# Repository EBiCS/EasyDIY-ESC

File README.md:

# EasyDIY ESC

Note: 'main' branch is under development, there is a change to use KiCad as compared to v0.5.2 (current HEAD of feature/v0_5_2, i.e. git SHA1 - e55e314)

The target for this EV motor controller is to power small EVs like EBikes or EScooters like Xiaomi M365, and offer better customizability and repairability.

## Main objectives:

* **Easy to build and repair DIY**: It uses DC-DC modules, a development board instead of an uC chip, SMD passive components are all 0805 or bigger, and ICs are SOIC8 or SOIC14. No fine pitch components.

* **Popular components:** Uses the popular Bluepill STM32F103 board, meaning it is easy to develop firmware for it. Uses popular components / footprints / pinouts. Meaning you should have no problems with part availability, and if you do, you will be able to change most parts with equivalents depending on availability or prefrence, without need to change the pcb layout.

* **Possible to add custom electronics:** For reusing this motor controller on different devices, you can extend the electrocnis with a custom header on top of the Bluepill. This means you can use all available pins and access and extend with: CAN, UARTs, etc.

* **Possibility to buy the SMD parts pre-soldered:** While we went to great extend do make this board easy to DIY by humans (as opposed to robots in a factory), we acknowledge there are many who lack the skill/time/motivation to solder all SMDs themselves. So all SMDs are on the same side, in large stock at lcsc (at the time of writing), so the board can be ordered with SMDs pre-assembled by JLCPCB for a decent price.

* **Compactness:** Despite using only big DIY friendly parts, we tried to keep the board as small as possible: ~ 73mm x 49mm

* **Good Power/Size ratio:** Our initial estimation (untested) is that the upper limit for phase current should be ~78A. As for max continuous “battery amps”, it heavily depends on the cooling!  

## ES Thread:
https://endless-sphere.com/forums/viewtopic.php?f=30&t=114537

## Building Tips:

### **Bus Bars**
Bus bars are recommended for anything else than very low current. (extra copper wires soldered to the exposed copper strips of the PCB, or at very least a lot of solder on the exposed strips)

### **Bulk electrolytic capacitors (XC.... )**
We went for a total of ~1000uF, which should be enough for most usecases. 
You need more capacitance the more power you plan to use, and the longer (and thinner) your battery wires are. So you can probably also get away with less if you have short thick battery wires.  
Choose voltage rating ~ 1.5x your max battery voltage for a long lifetime. For 48v nominal (54.6V max) battery voltage, 80V or more is recommended. 
The total capacitance of the electrolytic capacitors is more important than the exact combination of values. 1 big + 3 small is almost the same as 3 medium of the same total value. More smaller capacitors have the advantage of lower ESR, lower inductance, and redundancy in case one fails)

### **Bulk ceramic/MLC capacitors:  (XC.... )**
As much as possible. These need to compensate for the high frequency weakness of the electrolytic capacitors. Overrating voltage rating is recommended. (author chose 100V for the “default” for 3.3v, 5v and 12v). Definitely fill all open footprints. 

### **Capacitors - the rest**
Values are consolidated for easy buying. Voltage rating is 25V or higher regardless if they are on the 12v, 5v, or 3v3 rail on the default design, however you can choose a smaller voltage rating for the 5v and 3v3 rails..  
All parts are 0805 mlc (2 electrolytic exceptions, C8 and C10 from the 12v and 5v rails)

### **Snubbers (RSx, CSx)**
These are RC snubbers. **The current values for the R and C are random, they are here only for the footprints. Do not fit them (yet).** The real values (if necessary at all) will be computed after we build the controller and see what ringing we get. Purpose of the snubbers is to dampen that ringing. (if you choose different parts than the one we compute the snubbers for, you might need to compute the snubbers yourself). These components are not present in the pick-and-place or BOM files.

### **Optional Capacitors (OCx)**
All parts marked OCx are optional GS Capacitors for the mosfets. If you insist on using old/bad mosfets with high Crss, you'll need to compensate for that with additional Cgs. That being said, please avoid high Crss mosfets, and you don't need to use the OCx. We expect none of the recommended FETs to need these. These are footprints only to offer flexibility if needed. These components are not present in the pick-and-place or BOM files. 

### **FETs**
The default FETs are available from aliexpress at the time of writing. They are cheap and have good specs. (low Rds on, low Crss, 100v, etc). 
You can solder them “standing” on the the throughhole/module side, or bent flat on the opposite (smd) side. In either case, it is recommended that the thick part of the leads is in contact with (soldered to) the board. The thin part of the leads can carry significantly less current.

You can use a fet of your choosing, but please be aware that old Fets (such as the famous 4110 or 3077) have huge Crss, leading to a tiny Ciss/Crss ratio. This ratio needs to be bigger than roughly your max battery voltage, so you will need to compute and add the optional Cgs capacitors (OCx). Small Ciss/Crss results in ringing / parastic turn on (which leads to failure). 
That being said, it’s best to just use Fets with Ciss/Crss > ~100, nowadays they’re easy to find. See the spreadsheet with alternative parts. 

Attaching the FETs to a heatsink: the FETs need to be electrically isolated from the heatsink, but well connected thermally. The options for this are:
* Mica glass (“traditional option”, cheap, easy to find)
* Ceramics (saw this as a new option, never tried it)
* Polymer pads 
* Kapton Tape 

Unfortunately in focusing on making the board small we crammed the FETs very close together. This means some mica or ceramic pads will not fit - and it’s very hard to cut them afaik. So for this version we’re probably stuck with polymer / kapton. 

### **Testing**

* v0.5 build has been tested by mxlemming with MESC FOC firmware on F401CC black pill board

### **Known issues/limitations:**
* Mosfet temp sensor missing - you can add it to the expansion board. 
* Many connectors are not present (example: CAN)  - you can add them to the expansion board. 

## FAQ

* **What’s with those 2 solder jumpers?**
They are power for your uart-connected board. If it’s a 5v board, solder the 5v solder jumper, if it needs 3.3v solder the 3v3 jumper. Never solder both! 

* **Can you assemble it for me?**
You can get the SMD side pre-assembled at jlcpcb (at the time of design all parts were in stock for jlcpcb SMT service). So you’ll only need to solder the through-hole parts and the modules. Currently there is no plan on selling any assembled PCBs.

* **I want more power!!!**
This might not go well. So good luck, you’ll probably need it. Please don't blame us when it goes up in smoke. But do let us know how it goes. Disclamer aside, here are some basic suggestions:
   * Stack another 1mohm shunt on top of the other. This will double the max current you can read. 
   * Add thick bus bars to the board.
   * Add more/ bigger bulk caps!
   * Use appropriate wires (thick!) 

* **I want more voltage!!!!**
Realistic limit is 15s lipo. For more than that the ESC will need serious redesign.
Some bottlenecks that cross my mind: 
   * default 12v dc module is 72v limited, 
   * some of the recommended mosfets are not capable of more voltage, 
   * voltage sense divider needs adjustment, etc. 
   * PS: I would have loved to make it 20s capable, but did not find any small 100-12v DC-DC module. If you know of one, please let us know in our ES thread, and next version might be 20s / 74v capable. Also, I added 3 through hole pads for easy mounting of any 12V module via wires :)

* **Your part X is bad, I recommend Y!**
We tried to find cheap but decent parts for this controller. Cheap almost always implies a compromise in some other areas, so you might not like our pick :)
It should be fairly easy to switch to other parts on your own: we used mostly standard and popular footprints and packages
If you know better parts or have better solutions, please let us know on our ES thread. We like learning new things. 
....except if you’re going to suggest 3077 or 4110 mosfets. Those things are dinosaurs. They were the biggest baddest thing around during their time, but nowadays belong to a museum. Or a kid’s t-shirt. Please stop recommending them. See our thread for details.

* **Where can I buy parts?**
Lcsc.com, mouser.com. Aliexpress if needed. 
I designed this with jlcpcb smt assembly in mind, so all SMDs were in stock at lcsc when I designed the PCB. Also most of the Through-hole parts. 
Some exceptions, and where to buy them:
   * Default mosfets - aliexpress. 
   * 12v module - mouser
   * 5v module - aliexpress. There is a fixed voltage one, we recommend that one! 
   * Bluepill - aliexpress. Don’t know a better source these days. 
   * Jst headers - aliexpress
   * Bluepill headers - aliexpress

* **Why do the battery wires go in seemingly random places in the middle of the board?**
If you have the battery wires at the edge, then the full battery current will need to go through a portion of the battery “traces” of the PCB. I’ve placed them near the middle switch node, so with a tiny exception, the current through the traces is ⅓ of the battery current. 

* **This whole thing is amateur work!**
Yeah, totally true. We are amateurs working on a generic low power ESC for free. If by this you refer to any specific mistake / set of mistakes, we would love to know about it! Post in the ES thread. Thanks!

## Change log v0.5 -> v0.5.2

### Schematic
* Changes:
  * changed voltage sense resistors to 10x lower value (basic jlcpcb resistors -> cheaper)
  * removed pin 20 from GND (for blackpill compatibility)
  * removed thermal reliefs
  * replaced some parts with more cost-effective equivalents (basic parts jlcpcb)
  * changed diodes to a bigger more rugged version (more inline with the philosophy of this controller)
  * changed voltage sense divider so max read voltage is 100V (20s compatibility)
  * added circuitry for a ntc temp sensor for mosfets.
  * changed the electrolytic caps from the 12V and 5V rails to MLCC (still more capacitance than manufacturer recommends)
  * swapped ntc pins: MOSFET Temp -> A0, and Motor Temp -> A1 (for compatibility with EBiCS v2)
  * changed pinout of HALL JST connector - now you can use, additionally to a 6 pin connector for motors with temp NTC sensor, a 5pin connector on pins 1-5 and it will directly be compatible with the cable of a motor without temp sensor (M365 would be a popular example)
### PCB Design 
  * added 3 through hole pads for vbat, 12v, and gnd for easy connection with wires of any dc-dc module for more flexibility
  * moved JST connectors away from bluepill for better fitting (increased board width by 1mm)
  * many minor layout changes 

## Change log v0.1 -> v0.5

### Schematic
* Fixes:
  * added voltage divider for the voltage follower op-amp
  * added connection between the 3 2k2 resistors and 3V3 on hall sensor inputs
  * changed decoupling caps of the 3 power stages from VBAT-Shunt to VBAT-GND 

* Changes
  * replaced "default" mosfets with much better model
  * replaced shunts with 1mOhm (much lower value)
  * connected bluepill pin 20 to GND
  * changed the RC from the phase wire of the power stages to snubbers
  * replaced opamp with better model
  * changed Opamp 2 to be the voltage follower for easier routing
  * replaced vattery connectors with 2 pads for wire soldering
  * removed one of the connectors for hall sensors, replaced the other one with JST PH. 
  * pinout changes for leaving CAN pins free
  * replaced mini 360 with MP1584EN (is bigger, but there is a non-adjustable 5V version, which is less error-prone to use.)
  * changed all ceramic decoupling capacitors for 3v3 and 5v to 10uF 0805
  * changed all bootstrap capacitors to  10uF 0805
  * added 1 ceramic decoupling capacitor per power stage (for a total of 2) 
  * increased gain of opamps to 10 (from 8)
  * consolidated pullup R values to 2k2
  * consolidated many other C and R values
  * removed diode and cap from the hall sensor 5v rail
  * removed extension board headers (will be mounted on top of the bluepill on the same pins)
  * replaced electrolytic caps with bigger values and bigger voltage ratings

### PCB design:

* Fixes: 
  * Moved the decoupling capacitor close to the bus bars (GND was through a long thin trace which rendered it almost useless) 	

* Changes:
  * moved to 4 layer board (Ground Planes rule!)
  * moved the opamp non-inverting input resistors near the shunt - so they get the potential of that local ground (not of the GND near the opamp) 
  * stacked DC-DC modules
  * removed expansion board headers
  * added 3 JST PH headers for basic functions
  * moved vbat rail at the edge of the board and GND rail in the middle
  * major redesign of everything
  * greatly reduced the size

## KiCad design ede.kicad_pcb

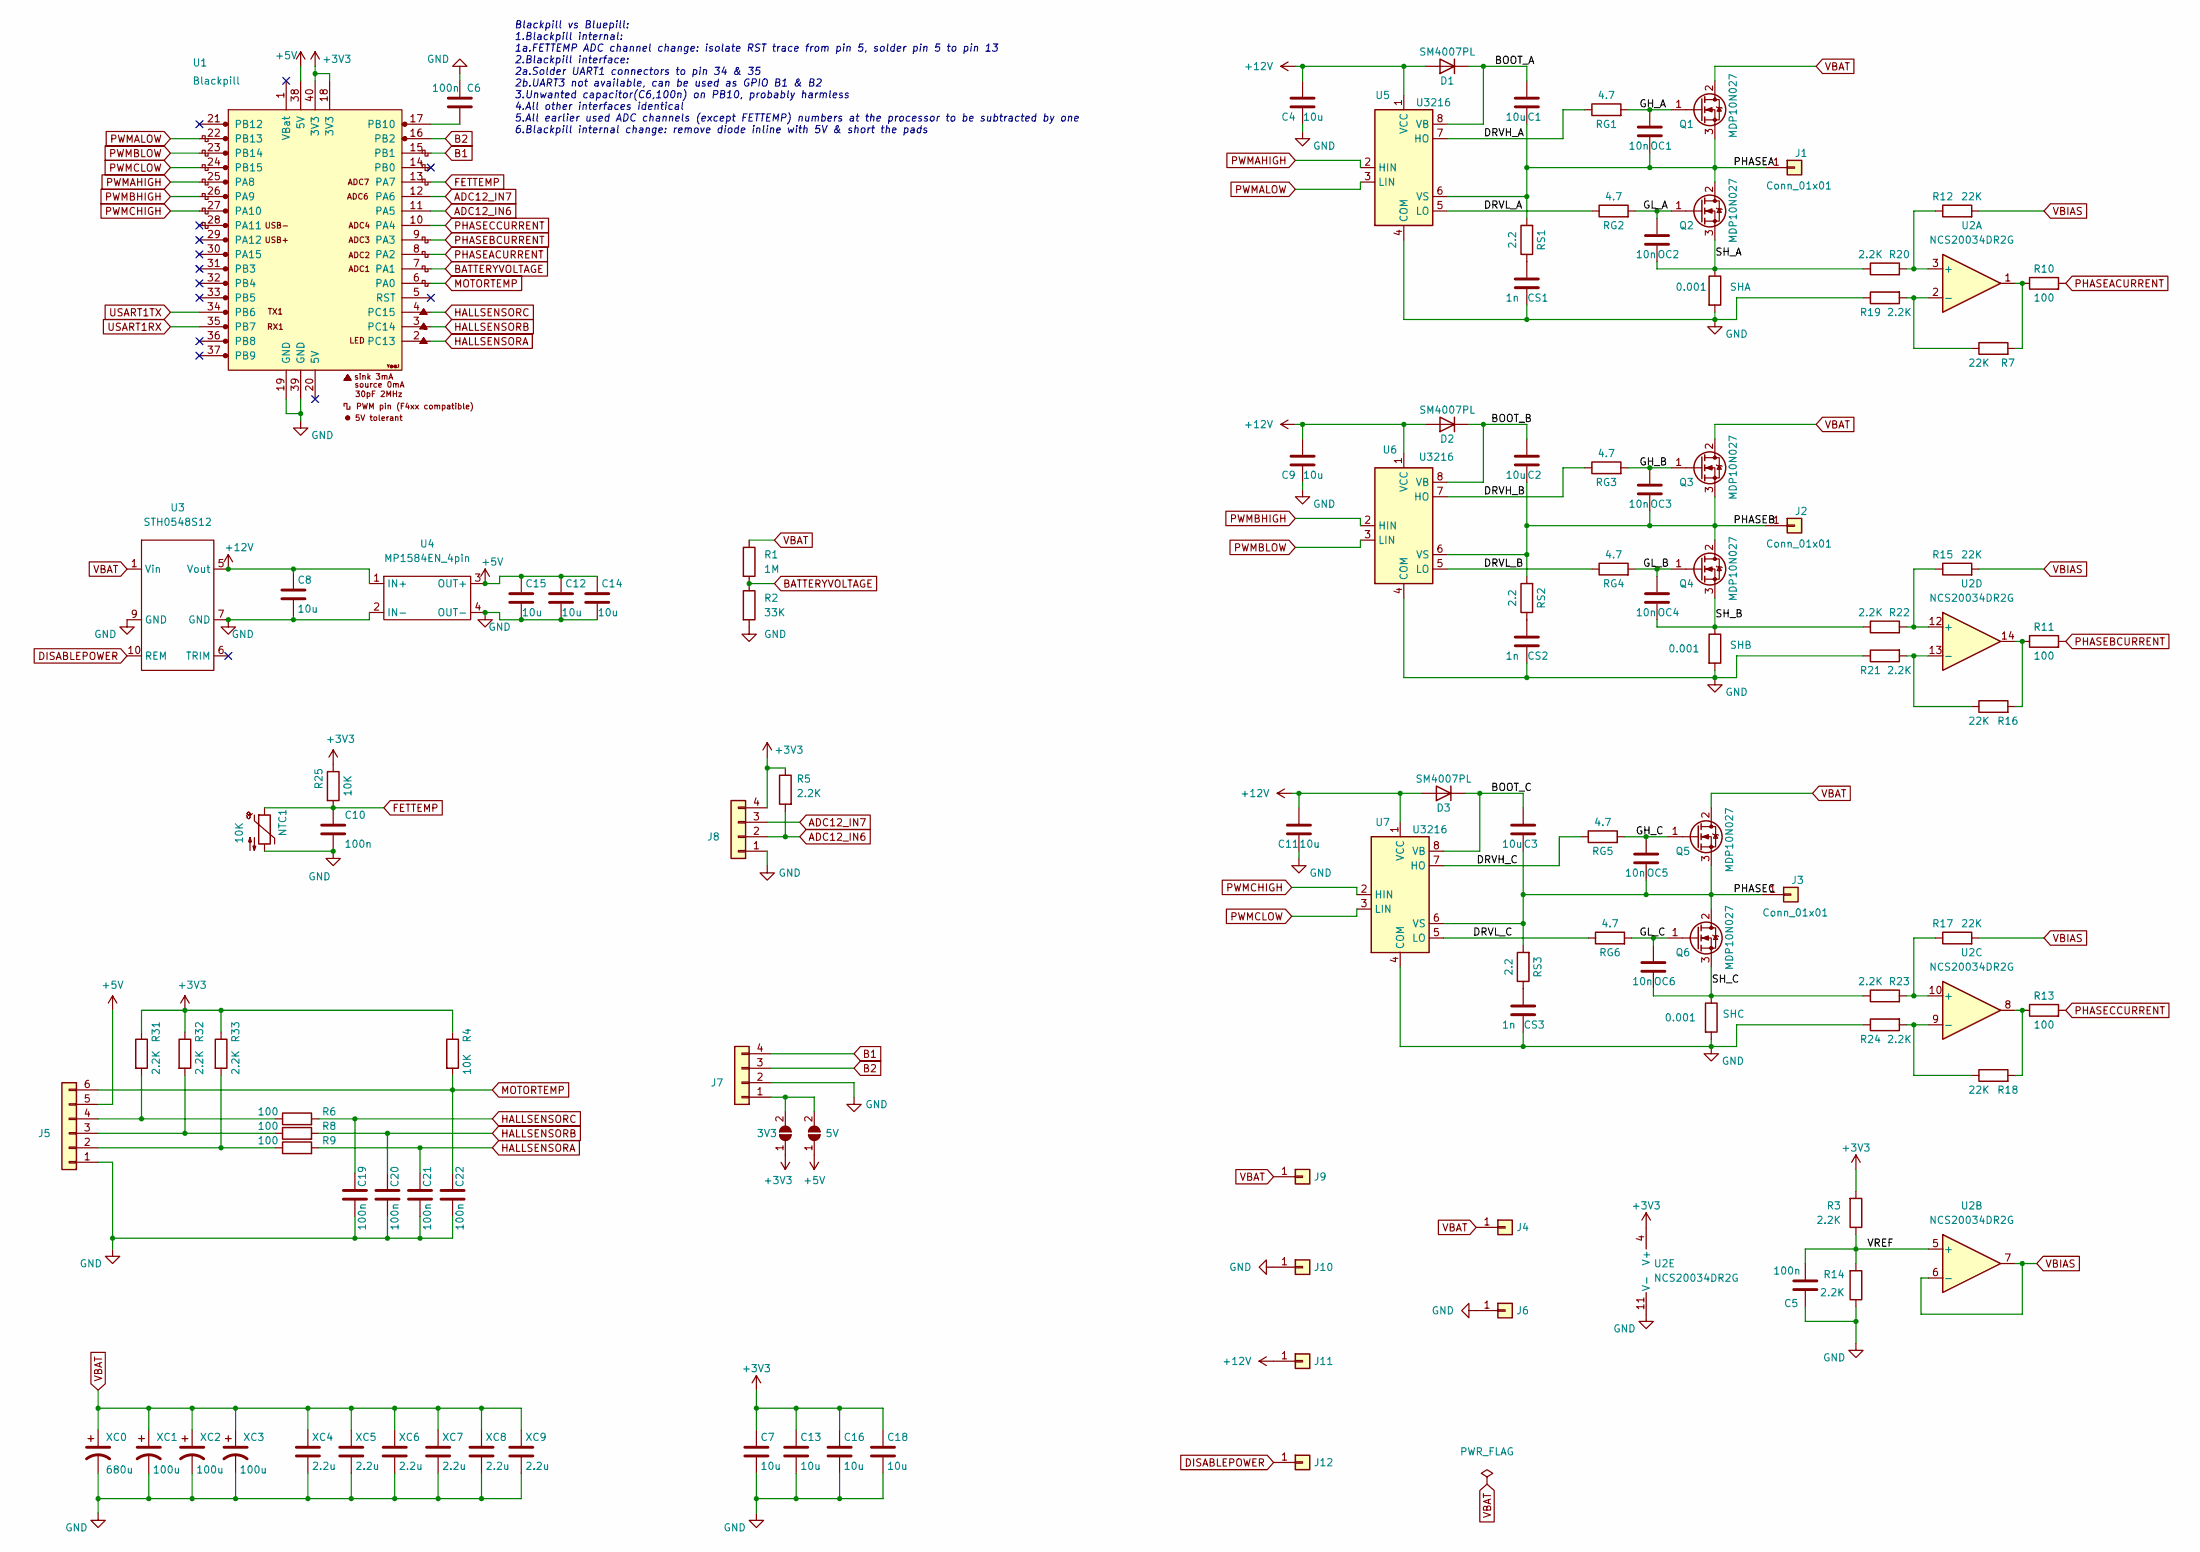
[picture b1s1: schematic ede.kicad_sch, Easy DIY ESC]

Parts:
C1, C2, C3, C4, C7, C8, C9, C11, C12, C13, C14, C15, C16, C18: 10u; C_0805_2012Metric_EDE
C5, C6, C10, C19, C20, C21, C22: 100n; C_0805_2012Metric_EDE
CS1, CS2, CS3: 1n; C_0805_2012Metric_EDE
D1, D2, D3: SM4007PL; D_SOD-123_EDE
J1, J2, J3, J4, J6: Conn_01x01; THT_1x_ID_2.8_OD_4
J5: Conn_01x06; JST_PH_B6B-PH-K_1x06_P2.00mm_Vertical_EDE
J7, J8: Conn_01x04; JST_PH_B4B-PH-K_1x04_P2.00mm_Vertical_EDE
J9, J10, J11: Conn_01x01; THT_1x_ID_1_OD_2
J12: Conn_01x01; TestPoint_Pad_D1.4mm_EDE
JP1, JP2: SolderJumper_2_Open; SolderJumper-2_small_EDE
NTC1: 10K; THT_2x_P2.54_ID_0.7_OD_1.3
OC1, OC2, OC3, OC4, OC5, OC6: 10n; C_0805_2012Metric_EDE
Q1, Q2, Q3, Q4, Q5, Q6: MDP10N027; TO-220-3_Vertical_EDE
R1: 1M; R_0805_2012Metric_EDE
R2: 33K; R_0805_2012Metric_EDE
R3, R5, R14, R19, R20, R21, R22, R23, R24, R31, R32, R33: 2.2K; R_0805_2012Metric_EDE
R4, R25: 10K; R_0805_2012Metric_EDE
R6, R8, R9, R10, R11, R13: 100; R_0805_2012Metric_EDE
R7, R12, R15, R16, R17, R18: 22K; R_0805_2012Metric_EDE
RG1, RG2, RG3, RG4, RG5, RG6: 4.7; R_0805_2012Metric_EDE
RS1, RS2, RS3: 2.2; R_0805_2012Metric_EDE
SH1, SH2, SH3: 0.001; R_2512_6332Metric_EDE
U1: Blackpill; YAAJ_Bluepill
U2: NCS20034DR2G; SOIC-14_3.9x8.7mm_P1.27mm_EDE
U3: STH0548S12
U4: MP1584EN_4pin
U5, U6, U7: U3216; SOIC-8_3.9x4.9mm_P1.27mm_EDE
XC0: 680u; CP_Radial_D12.5mm_P5.00mm_EDE
XC1, XC2, XC3: 100u; CP_Radial_D8.0mm_P3.50mm_EDE
XC4, XC5, XC6, XC7, XC8, XC9: 2.2u; C_1206_3216Metric_EDE

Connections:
+3V3: C7.1, C13.1, C16.1, C18.1, J8.4, JP1.1 (A), R3.2, R4.1, R5.1, R25.1, R31.1, R32.1, R33.1, U1.18 (3V3), U1.40 (3V3), U2.4 (V+)
+5V: C12.1, C14.1, C15.1, J5.5, JP2.1 (A), U1.38 (5V), U4.3 (OUT+)
+12V: C4.1, C8.1, C9.1, C11.1, D1.2 (A), D2.2 (A), D3.2 (A), J11.1, U3.5 (Vout), U4.1 (IN+), U5.1 (VCC), U6.1 (VCC), U7.1 (VCC)
/BOOT_A: C1.1, D1.1 (K), U5.8 (VB)
/BOOT_B: C2.1, D2.1 (K), U6.8 (VB)
/BOOT_C: C3.1, D3.1 (K), U7.8 (VB)
/DRVH_A: RG1.1, U5.7 (HO)
/DRVH_B: RG3.1, U6.7 (HO)
/DRVH_C: RG5.1, U7.7 (HO)
/DRVL_A: RG2.1, U5.5 (LO)
/DRVL_B: RG4.1, U6.5 (LO)
/DRVL_C: RG6.1, U7.5 (LO)
/GH_A: OC1.1, Q1.1 (G), RG1.2
/GH_B: OC3.1, Q3.1 (G), RG3.2
/GH_C: OC5.1, Q5.1 (G), RG5.2
/GL_A: OC2.1, Q2.1 (G), RG2.2
/GL_B: OC4.1, Q4.1 (G), RG4.2
/GL_C: OC6.1, Q6.1 (G), RG6.2
/PHASEA: C1.2, J1.1, OC1.2, Q1.3 (S), Q2.2 (D), RS1.2, U5.6 (VS)
/PHASEB: C2.2, J2.1, OC3.2, Q3.3 (S), Q4.2 (D), RS2.2, U6.6 (VS)
/PHASEC: C3.2, J3.1, OC5.2, Q5.3 (S), Q6.2 (D), RS3.2, U7.6 (VS)
/SH_A: OC2.2, Q2.3 (S), R20.1, SH1.1
/SH_B: OC4.2, Q4.3 (S), R22.1, SH2.1
/SH_C: OC6.2, Q6.3 (S), R23.1, SH3.1
/VREF: C5.2, R3.1, R14.2, U2.5 (+)
ADC12_IN6: J8.2, R5.2, U1.11 (PA6)
ADC12_IN7: J8.3, U1.12 (PA7)
BATTERYVOLTAGE: R1.2, R2.1, U1.7 (PA2)
DISABLEPOWER: J12.1, U3.10 (REM)
FETTEMP: C10.1, NTC1.1, R25.2, U1.5 (PA0), U1.13 (PA7)
GND: C4.2, C5.1, C6.2, C7.2, C8.2, C9.2, C10.2, C11.2, C12.2, C13.2, C14.2, C15.2, C16.2, C18.2, C19.2, C20.2, C21.2, C22.2, CS1.2, CS2.2, CS3.2, J5.1, J6.1, J7.2, J8.1, J10.1, NTC1.2, R2.2, R14.1, R19.1, R21.1, R24.1, SH1.2, SH2.2, SH3.2, U1.19 (GND), U1.39 (GND), U2.11 (V-), U3.7 (GND), U3.9 (GND), U4.2 (IN-), U4.4 (OUT-), U5.4 (COM), U6.4 (COM), U7.4 (COM), XC0.2, XC1.2, XC2.2, XC3.2, XC4.2, XC5.2, XC6.2, XC7.2, XC8.2, XC9.2
HALLSENSORA: C21.1, R9.2, U1.2 (PC13)
HALLSENSORB: C20.1, R8.2, U1.3 (PC14)
HALLSENSORC: C19.1, R6.2, U1.4 (PC15)
MOTORTEMP: C22.1, J5.6, R4.2, U1.6 (PA1)
unnamed: C6.1, U1.17 (RST)
unnamed: CS1.1, RS1.1
unnamed: CS2.1, RS2.1
unnamed: CS3.1, RS3.1
unnamed: J5.2, R9.1, R33.2
unnamed: J5.3, R8.1, R32.2
unnamed: J5.4, R6.1, R31.2
unnamed: J7.1, JP1.2 (B), JP2.2 (B)
unnamed: R7.2, R10.1, U2.1
unnamed: R11.1, R16.2, U2.14
unnamed: R12.1, R20.2, U2.3 (+)
unnamed: R13.1, R18.2, U2.8
unnamed: R15.1, R22.2, U2.12 (+)
unnamed: R16.1, R21.2, U2.13 (-)
unnamed: R17.1, R23.2, U2.10 (+)
unnamed: R18.1, R24.2, U2.9 (-)
unnamed: R7.1, R19.2, U2.2 (-)
PHASEACURRENT: R10.2, U1.8 (PA3)
PHASEBCURRENT: R11.2, U1.9 (PA4)
PHASECCURRENT: R13.2, U1.10 (PA5)
PWMAHIGH: U1.25 (PA8), U5.2 (HIN)
PWMALOW: U1.22 (PB13), U5.3 (LIN)
PWMBHIGH: U1.26 (PA9), U6.2 (HIN)
PWMBLOW: U1.23 (PB14), U6.3 (LIN)
PWMCHIGH: U1.27 (PA10), U7.2 (HIN)
PWMCLOW: U1.24 (PB15), U7.3 (LIN)
USART3RX: J7.3, U1.16 (PB11)
USART3TX: J7.4, U1.15 (PB10)
VBAT: J4.1, J9.1, Q1.2 (D), Q3.2 (D), Q5.2 (D), R1.1, U3.1 (Vin), XC0.1, XC1.1, XC2.1, XC3.1, XC4.1, XC5.1, XC6.1, XC7.1, XC8.1, XC9.1
VBIAS: R12.2, R15.2, R17.2, U2.6 (-), U2.7

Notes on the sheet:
Blackpill vs Bluepill: 1.Blackpill internal: 1a.FETTEMP ADC channel change: isolate RST trace from pin 5, solder pin 5 to pin 13 2.Blackpill interface: 2a.Solder UART1 connectors to pin 34 & 35 2b.UART3 not available, can be used as GPIO B1 & B2 3.Unwanted capacitor(C6,100n) on PB10, probably harml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

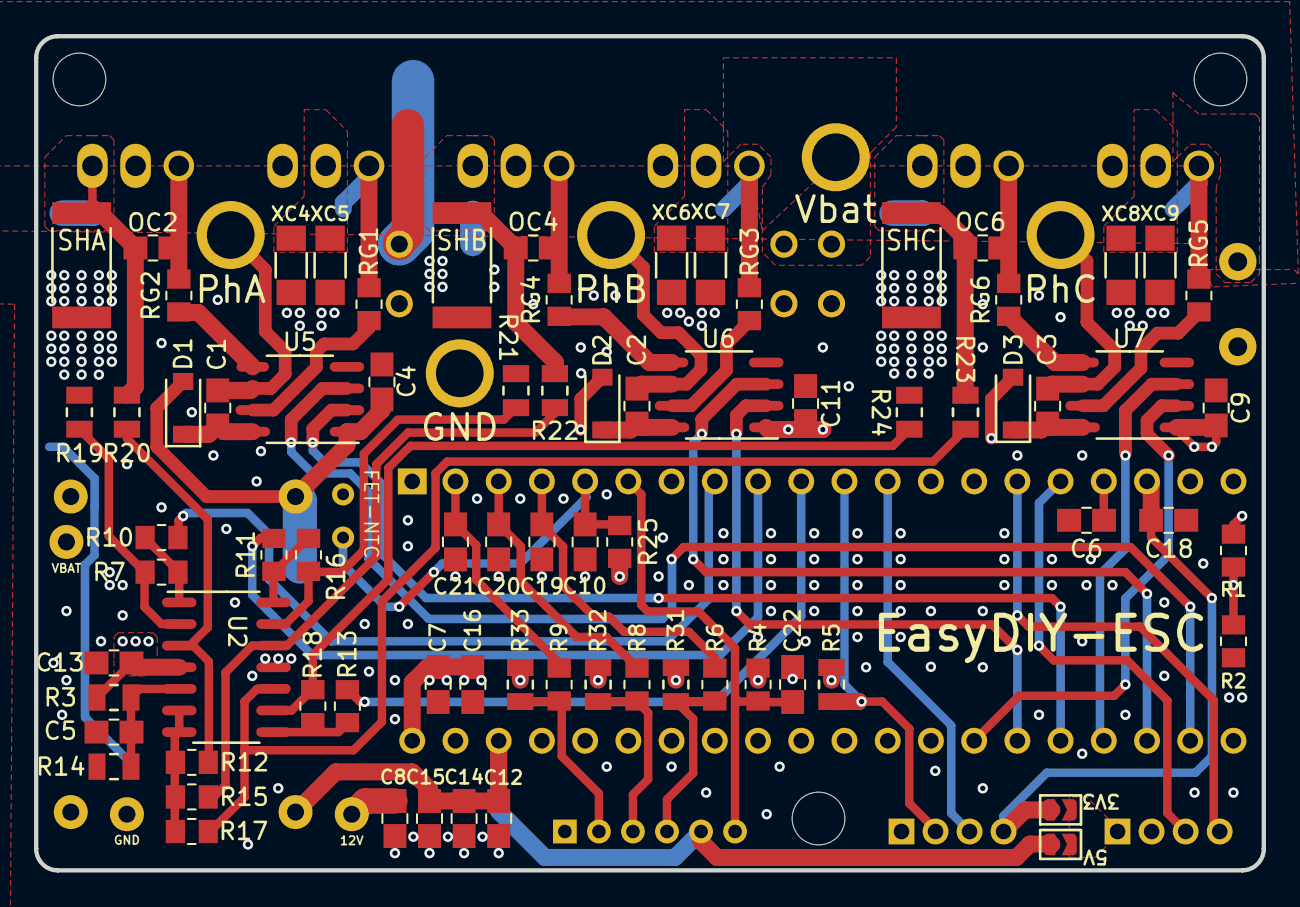
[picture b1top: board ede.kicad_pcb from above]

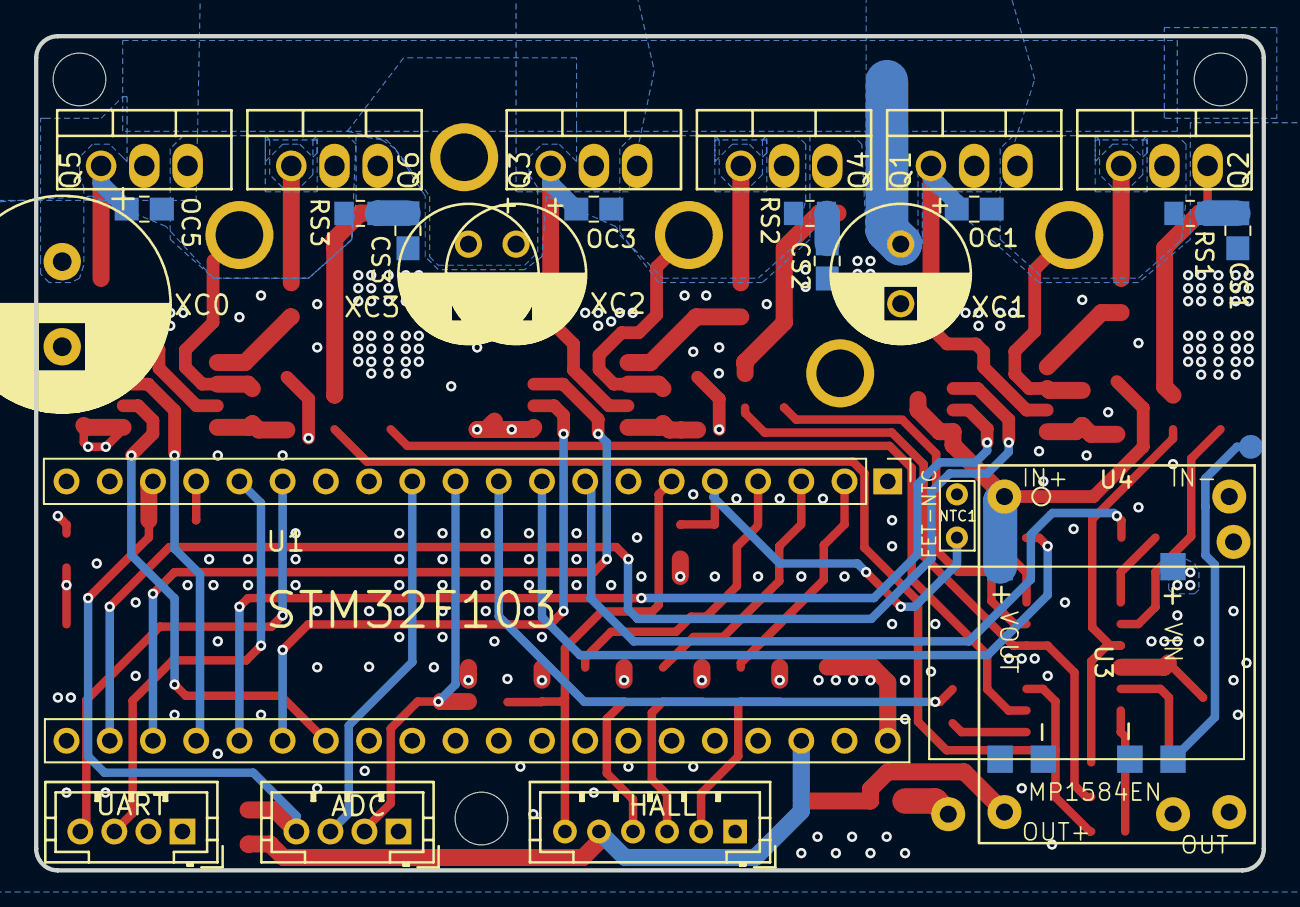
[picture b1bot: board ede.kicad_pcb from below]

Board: 4 copper layers, 72.1 x 49.0 mm, 111 parts (27 on the bottom side), 65 nets.

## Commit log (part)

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2021-12-31 Added project source files, build PCB files as also prject README notes
2021-12-31 Note about issue on schematic and PCB
2022-01-24 Updated notes about current board version, as also added top and bottom layer PDFs, as also the schematic
2022-01-27 Added some pictures of the prototype as also improved the notes. The motor runs well, both the autodetection as also running using a throttle
2022-01-27 Updated current state
2022-01-27 Added suggestion to free CAN pins
2022-03-19 added v-.5 folder, changed readme file
2022-03-19 added actual content to the v0.5 folder
2022-04-17 v0_5_2 - many minor improvements
2022-09-21 gitignore
2022-10-12 sch, pcb: add date
2022-10-12 EasyDIY-ESC KiCad adaptation
2022-10-12 Add LICENSE & minimal README
2022-10-12 pcb: B.Cu & In2.Cu fix
2022-10-12 prepare for library as submodule
2022-10-12 submodule: integrate library
2022-10-13 pcb: Mask for busbars & phase connectors
2022-10-15 README: mention main under development & append w/ the one from v0.5.2
2022-10-15 pcb: avoid sharp edges
2022-10-15 README: rough update to the current state
2022-10-27 Update README.md
    Factual corrections in readme. Contained some errors
2022-10-30 Update README.md
    small factual mistake corrected in documentation
2022-11-04 pcb: In2.Cu gnd zone continuous b/n FET legs
    zone minimum width reduced to 0.2
2022-11-04 pcb: use drill/place file origin
    To compare easily with v0.5.2 gerbers
2022-11-04 pcb: bring In2.Cu +12V busbar more similar to v0.5.2
2022-11-04 pcb: T.Cu Mtr temp resistor 3.3V via to track improvement
2022-11-04 pcb: alter R0805 footprints on B.Cu as per reference
2022-11-04 pcb: fix DRC clearance violation error
2022-11-04 pcb: integrate C0805 library pad dimension swap
2022-11-04 pcb: alter some of the R0805 footprint as per reference
2022-11-04 pcb: avoid more bends on Ph C driver to bypass cap route
2022-11-04 pcb : uncheck 'include netlist attributes'
    To be on par with JLCPCB recommended setting.
    Though extended X2 format is not in recommended settings, since it is mentioned
    don't care in JLCPCB docs, it has been enabled.
2022-11-04 submodule: C0805 fix & R0805 small footprint
